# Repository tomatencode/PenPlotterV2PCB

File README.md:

# Pen Plotter Controller Board

Eine selbst entworfene PCB-Steuerplatine für einen DIY Pen Plotter, entwickelt in KiCad. Die Platine steuert zwei Schrittmotoren für die XY-Bewegung, einen Servo für den Stifthub und übernimmt Benutzerführung sowie Energiemanagement vollständig auf einer einzigen Platine.

## Funktionen

- **ESP32** – Haupt-Mikrocontroller (Breakout aufgelötet) für Bewegungssteuerung und Logik
- **2× TMC2209** – Schrittmotortreiber (Breakouts aufgelötet) mit UART-Konfiguration, stealthChop und stallGuard
- **SG90 Servo** – Stift-Auf/Ab-Mechanismus
- **I2C LCD-Display** – Angeschlossen über Steckverbinder
- **Drehgeber** – Manuelle Steuerung und Menünavigation über Steckverbinder
- **Buzzer** – Akustisches Feedback
- **5V Buck Converter** – (Breakout aufgelötet) Erzeugt die interne 5V-Versorgungsschiene aus 24V
- **24V DC-Eingang** – Versorgung über externen Transformator (DC-Hohlbuchse)

## Stromversorgungsarchitektur

| Schiene | Quelle                          | Verbraucher                            |
|---------|---------------------------------|----------------------------------------|
| 24 V    | Externer Transformator (DC-Buchse) | TMC2209 Motorspannung               |
| 5 V     | Buck Converter Breakout         | ESP32, Servo, Buzzer, LCD              |
| 3,3 V   | Interner LDO des ESP32          | TMC2209 Logikspannung, Drehgeber       |

## Platinenübersicht

### Schaltplan

### PCB-Layout

### 3D-Ansicht

## Entwickelt mit

- [KiCad](https://www.kicad.org/) – Schaltplan und PCB-Layout

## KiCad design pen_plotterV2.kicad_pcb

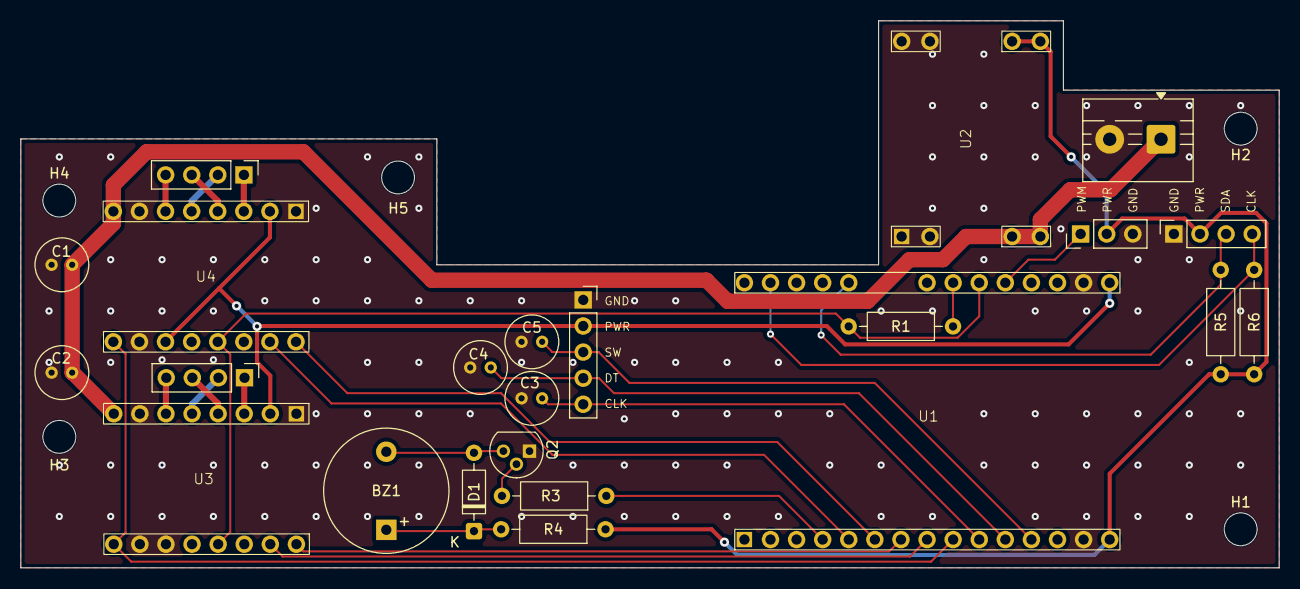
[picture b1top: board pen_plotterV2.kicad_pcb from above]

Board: 2 copper layers, 122.5 x 53.2 mm, 28 parts (0 on the bottom side), 29 nets.

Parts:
BZ1: Buzzer; Buzzer_12x9.5RM7.6
C1, C2, C3, C4, C5: 100u; C_Radial_D5.0mm_H7.0mm_P2.00mm
D1: 1N4148; D_DO-35_SOD27_P7.62mm_Horizontal
H1, H2, H3, H4, H5: MountingHole; MountingHole_3.2mm_M3
J1: Conn_01x02; TerminalBlock_MaiXu_MX126-5.0-02P_1x02_P5.00mm
J2, J3: Conn_01x04_Pin; PinHeader_1x04_P2.54mm_Vertical
J5: Conn_01x05_Socket; PinSocket_1x05_P2.54mm_Vertical
J6: Conn_01x04_Socket; PinSocket_1x04_P2.54mm_Vertical
J7: Conn_01x03_Pin; PinHeader_1x03_P2.54mm_Vertical
Q2: SS8050; TO-92
R1: 1k; R_Axial_DIN0207_L6.3mm_D2.5mm_P10.16mm_Horizontal
R3: 10k; R_Axial_DIN0207_L6.3mm_D2.5mm_P10.16mm_Horizontal
R4: 100R; R_Axial_DIN0207_L6.3mm_D2.5mm_P10.16mm_Horizontal
R5, R6: 5k1; R_Axial_DIN0207_L6.3mm_D2.5mm_P10.16mm_Horizontal
U1: ESP32 Breakout; ESP32 Bev Board
U2: 5v_Buc_Breakout; 5V Buc Breakout
U3, U4: TMC2209_Breakout; TMC2209 Breakout

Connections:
+3V3: J5.2, U1.30 (3v3), U3.2 (VDD), U4.2 (VDD), U4.14 (MS2)
+5V: J6.2, J7.2, R4.1, R5.1, R6.2, U1.15 (VIN), U2.4 (+Out)
+24V: C1.1, C2.1, J1.1, U2.2 (+IN), U3.8 (VM), U4.8 (VM)
/Buzzer: R3.1, U1.4 (D34)
/DIR1: U1.7 (D33), U3.9 (DIR)
/DIR2: U1.6 (D32), U4.9 (DIR)
/LcdCLK: J6.4, R6.1, U1.17 (D22)
/LcdSDA: J6.3, R5.2, U1.20 (D21)
/PWMservo: J7.1, U1.26 (D4)
/RotCLK: C3.1, J5.5, U1.10 (D27)
/RotDT: C4.1, J5.4, U1.11 (D14)
/RotSW: C5.1, J5.3, U1.12 (D12)
/STP1: U1.8 (D25), U3.10 (STP)
/STP2: U1.5 (D35), U4.10 (STP)
/UART: R1.2, U1.25 (D16), U3.12 (UART), U4.12 (UART)
/~ENstp: U1.9 (D26), U3.16 (~EN), U4.16 (~EN)
GND: C1.2, C2.2, C3.2, C4.2, C5.2, J1.2, J5.1, J6.1, J7.3, Q2.1 (E), U1.14 (GND), U1.29 (GND), U2.1 (-IN), U2.3 (-Out), U3.1 (GND), U3.7 (GND), U3.14 (MS2), U3.15 (MS1), U4.1 (GND), U4.7 (GND), U4.15 (MS1)
unnamed: BZ1.1 (+), D1.1 (K), R4.2
unnamed: BZ1.2 (-), D1.2 (A), Q2.3 (C)
unnamed: J2.1, U3.3 (1B)
unnamed: J2.2, U3.5 (2A)
unnamed: J2.3, U3.4 (1A)
unnamed: J2.4, U3.6 (2B)
unnamed: J3.1, U4.3 (1B)
unnamed: J3.2, U4.5 (2A)
unnamed: J3.3, U4.4 (1A)
unnamed: J3.4, U4.6 (2B)
unnamed: Q2.2 (B), R3.2
unnamed: R1.1, U1.24 (D17)

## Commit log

2026-05-24 Remove backup folder and add to gitignore
2026-05-24 remove production zip and add to gitignore
